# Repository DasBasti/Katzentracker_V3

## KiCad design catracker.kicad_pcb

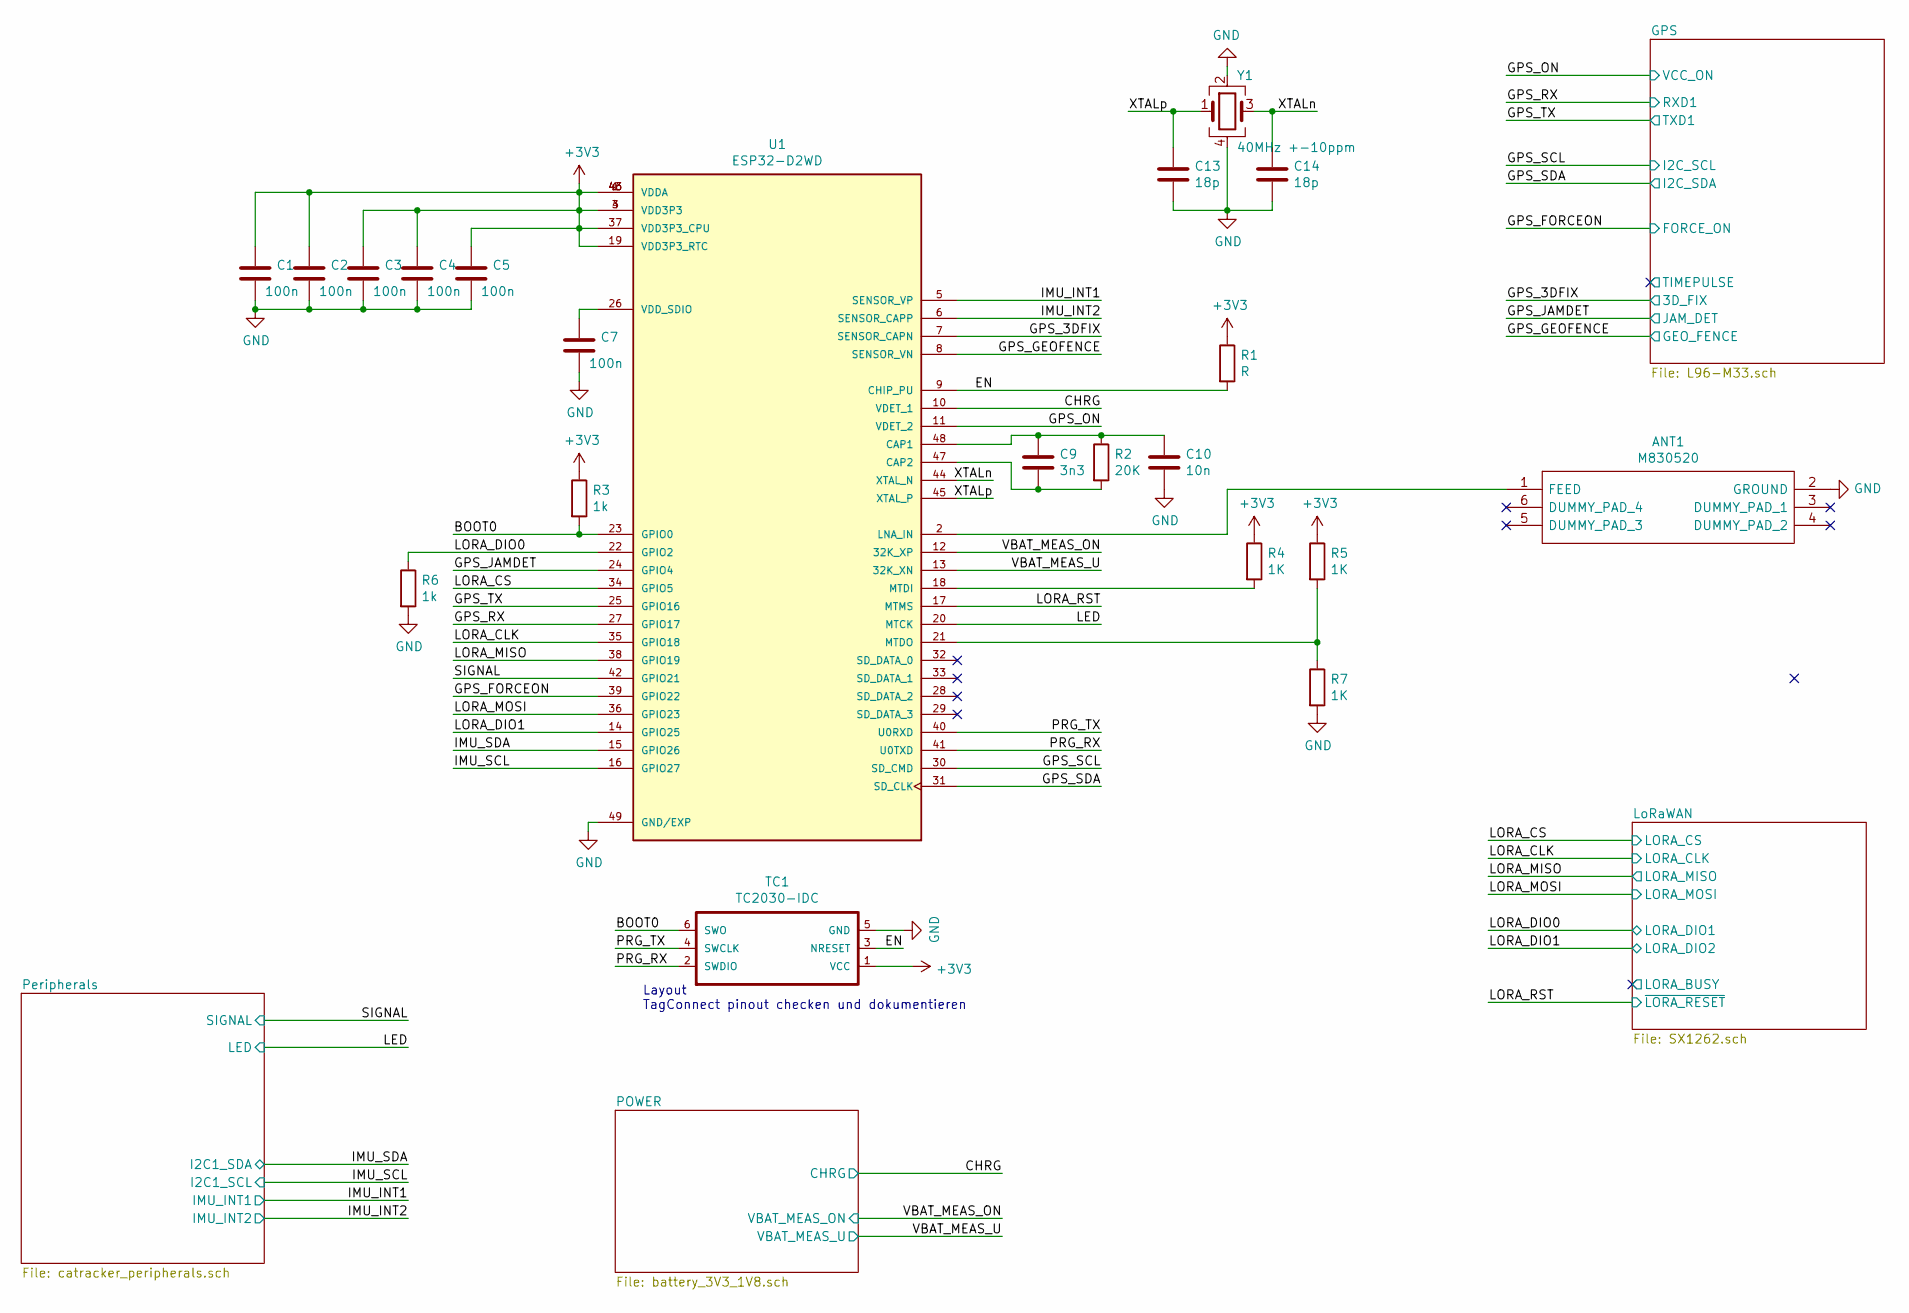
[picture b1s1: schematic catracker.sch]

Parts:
ANT1: M830520; Manufacturer_Part_Number M830520; Mouser Part Number 581-M830520
C1, C2, C3, C4, C5, C7: 100n; C_0402_1005Metric
C9: 3n3; C_0402_1005Metric
C10: 10n; C_0402_1005Metric
C13, C14: 18p; C_0402_1005Metric
R1: R; R_0402_1005Metric
R2: 20K; R_0402_1005Metric
R3, R6: 1k; R_0402_1005Metric
R4, R5, R7: 1K; R_0402_1005Metric
TC1: TC2030-IDC; Tag-Connect_TC2030-IDC-NL_2x03_P1.27mm_Vertical
U1: ESP32-D2WD; QFN-48-1EP_5x5mm_P0.35mm_EP3.7x3.7mm; PARTREV 2.9
Y1: 40MHz +-10ppm; Crystal_SMD_2520-4Pin_2.5x2.0mm

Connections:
+3V3: C1.1, C2.1, C3.1, C4.1, C5.1, R1.1, R3.1, R4.1, R5.1, TC1.1 (VCC), U1.1 (VDDA), U1.3 (VDD3P3), U1.4 (VDD3P3), U1.19 (VDD3P3_RTC), U1.37 (VDD3P3_CPU), U1.43 (VDDA), U1.46 (VDDA); also elsewhere on the board
/BOOT0: R3.2, TC1.6 (SWO), U1.23 (GPIO0)
/CHRG: U1.10 (VDET_1); also elsewhere on the board
/EN: R1.2, TC1.3 (NRESET), U1.9 (CHIP_PU)
/GPS_3DFIX: U1.7 (SENSOR_CAPN); also elsewhere on the board
/GPS_FORCEON: U1.39 (GPIO22); also elsewhere on the board
/GPS_GEOFENCE: U1.8 (SENSOR_VN); also elsewhere on the board
/GPS_JAMDET: U1.24 (GPIO4); also elsewhere on the board
/GPS_ON: U1.11 (VDET_2); also elsewhere on the board
/GPS_RX: U1.27 (GPIO17); also elsewhere on the board
/GPS_SCL: U1.30 (SD_CMD); also elsewhere on the board
/GPS_SDA: U1.31 (SD_CLK); also elsewhere on the board
/GPS_TX: U1.25 (GPIO16); also elsewhere on the board
/IMU_INT1: U1.5 (SENSOR_VP); also elsewhere on the board
/IMU_INT2: U1.6 (SENSOR_CAPP); also elsewhere on the board
/IMU_SCL: U1.16 (GPIO27); also elsewhere on the board
/IMU_SDA: U1.15 (GPIO26); also elsewhere on the board
/LED: U1.20 (MTCK); also elsewhere on the board
/LORA_CLK: U1.35 (GPIO18); also elsewhere on the board
/LORA_CS: U1.34 (GPIO5); also elsewhere on the board
/LORA_DIO0: R6.1, U1.22 (GPIO2); also elsewhere on the board
/LORA_DIO1: U1.14 (GPIO25); also elsewhere on the board
/LORA_MISO: U1.38 (GPIO19); also elsewhere on the board
/LORA_MOSI: U1.36 (GPIO23); also elsewhere on the board
/LORA_RST: U1.17 (MTMS); also elsewhere on the board
/PRG_RX: TC1.2 (SWDIO), U1.41 (U0TXD)
/PRG_TX: TC1.4 (SWCLK), U1.40 (U0RXD)
/SIGNAL: U1.42 (GPIO21); also elsewhere on the board
/VBAT_MEAS_ON: U1.12 (32K_XP); also elsewhere on the board
/VBAT_MEAS_U: U1.13 (32K_XN); also elsewhere on the board
/XTALn: C14.1, U1.44 (XTAL_N), Y1.3
/XTALp: C13.1, U1.45 (XTAL_P), Y1.1
GND: ANT1.2 (GROUND), C1.2, C2.2, C3.2, C4.2, C5.2, C7.2, C10.2, C13.2, C14.2, R6.2, R7.2, TC1.5 (GND), U1.49 (GND/EXP), Y1.2, Y1.4; also elsewhere on the board
unnamed: ANT1.1 (FEED), U1.2 (LNA_IN)
unnamed: C7.1, U1.26 (VDD_SDIO)
unnamed: C9.2, R2.2, U1.47 (CAP2)
unnamed: C9.1, C10.1, R2.1, U1.48 (CAP1)
unnamed: R4.2, U1.18 (MTDI)
unnamed: R5.2, R7.1, U1.21 (MTDO)

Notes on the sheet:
Layout TagConnect pinout checken und dokumentieren

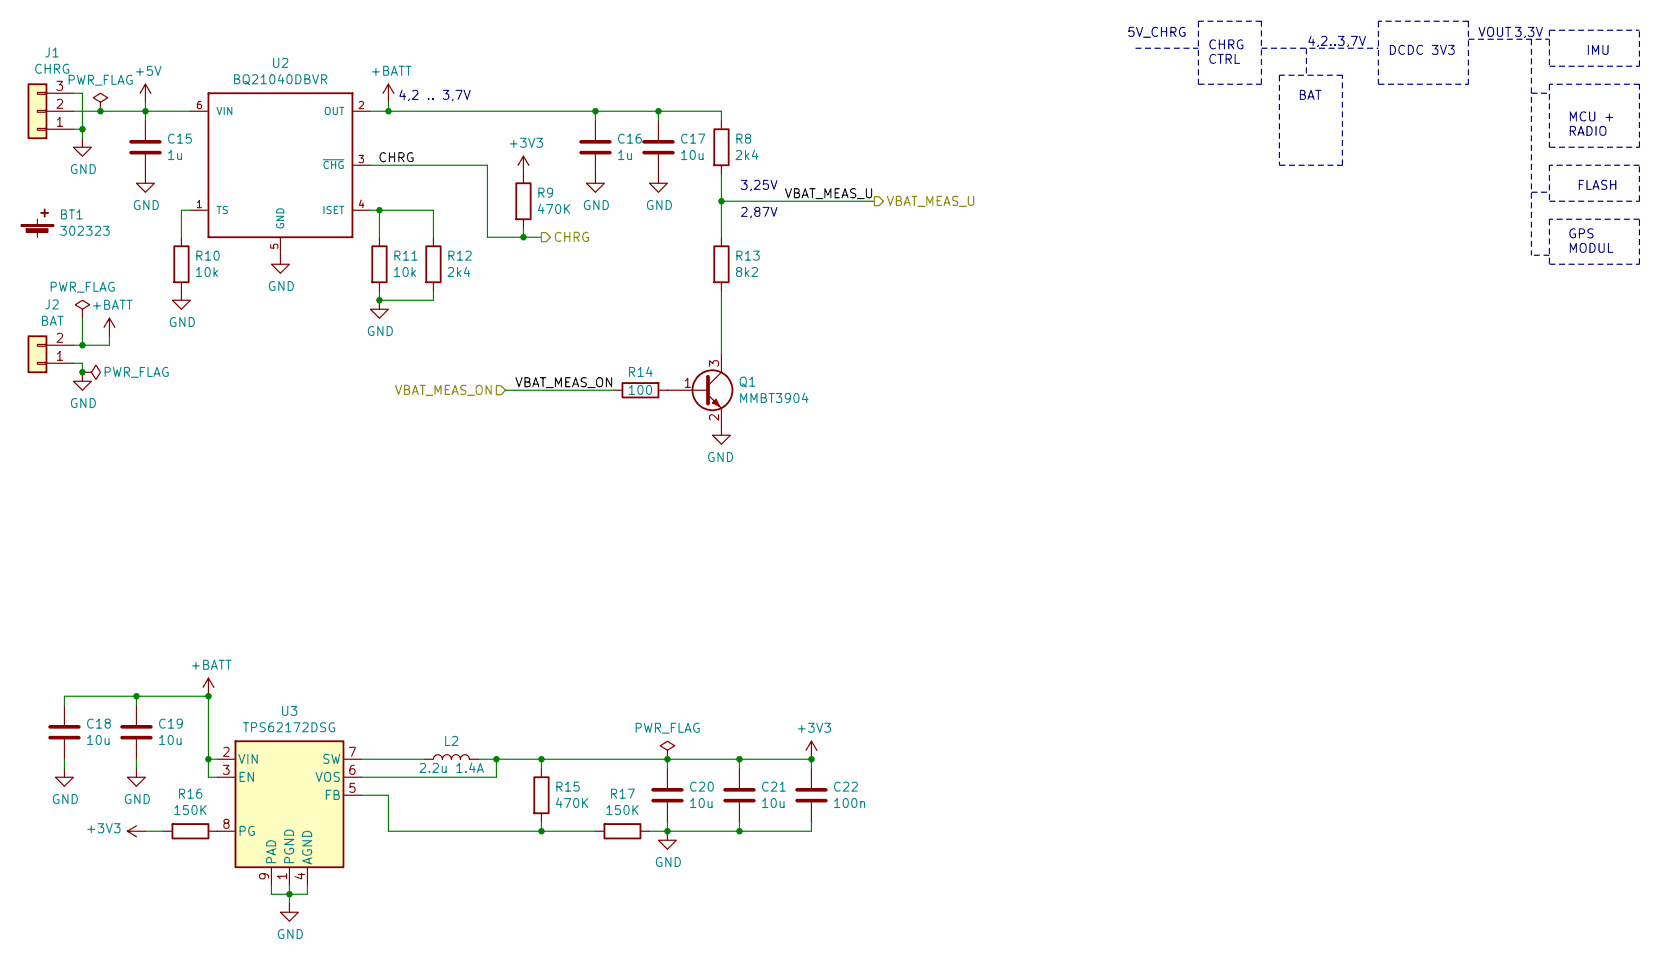
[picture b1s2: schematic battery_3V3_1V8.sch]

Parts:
BT1: 302323; LiPo_302323
C15, C16: 1u; C_0603_1608Metric; MPN 0603DC105MAT2A
C17, C18, C19, C20: 10u; C_0603_1608Metric; MPN GRM188R60J106ME84J
C21: 10u; C_0603_1608Metric; MPN 0603DC105MAT2A
C22: 100n; C_0402_1005Metric; MPN C1608X7R1V105K080AC
J1: CHRG; Magnetic_Charger_Clip
J2: BAT; PinSocket_1x02_P2.00mm_Vertical
L2: 2.2u 1.4A; L_0805_2012Metric; MPN AISC-0805F-2R2G-T
Q1: MMBT3904; SOT-23; MPN MMBT3904,215
R8, R12: 2k4; R_0402_1005Metric; MPN CRCW060310K0JNEAC
R9, R15: 470K; R_0402_1005Metric; MPN RC0603JR-138K2L
R10, R11: 10k; R_0402_1005Metric; MPN CRCW060310K0JNEAC
R13: 8k2; R_0402_1005Metric; MPN RC0603JR-138K2L
R14: 100; R_0402_1005Metric; MPN AC0603FR-13100RL
R16, R17: 150K; R_0402_1005Metric
U2: BQ21040DBVR; SOT-23-6; MPN BQ21040DBVR
U3: TPS62172DSG; WSON-8-1EP_2x2mm_P0.5mm_EP0.9x1.6mm_ThermalVias

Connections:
+3V3: C20.1, C21.1, C22.1, L2.2, R9.1, R15.1, R16.2, U3.6 (VOS); also elsewhere on the board
+5V: C15.1, J1.2, U2.6 (VIN)
+BATT: C16.1, C17.1, C18.1, C19.1, J2.2, R8.1, U2.2 (OUT), U3.2 (VIN), U3.3 (EN); also elsewhere on the board
/CHRG: R9.2, U2.3 (~CHG~); also elsewhere on the board
/VBAT_MEAS_ON: R14.1; also elsewhere on the board
/VBAT_MEAS_U: R8.2, R13.1; also elsewhere on the board
GND: C15.2, C16.2, C17.2, C18.2, C19.2, C20.2, C21.2, C22.2, J1.1, J1.3, J2.1, Q1.2 (E), R10.2, R11.2, R12.2, R17.1, U2.5 (GND), U3.1 (PGND), U3.4 (AGND), U3.9 (PAD); also elsewhere on the board
unnamed: L2.1, U3.7 (SW)
unnamed: Q1.1 (B), R14.2
unnamed: Q1.3 (C), R13.2
unnamed: R10.1, U2.1 (TS)
unnamed: R11.1, R12.1, U2.4 (ISET)
unnamed: R15.2, R17.2, U3.5 (FB)
unnamed: R16.1, U3.8 (PG)

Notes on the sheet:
3,25V
2,87V
4,2 .. 3,7V
FLASH
3,3V
4,2..3,7V
VOUT
IMU
MCU + RADIO
DCDC 3V3
5V_CHRG
CHRG CTRL
BAT
GPS MODUL

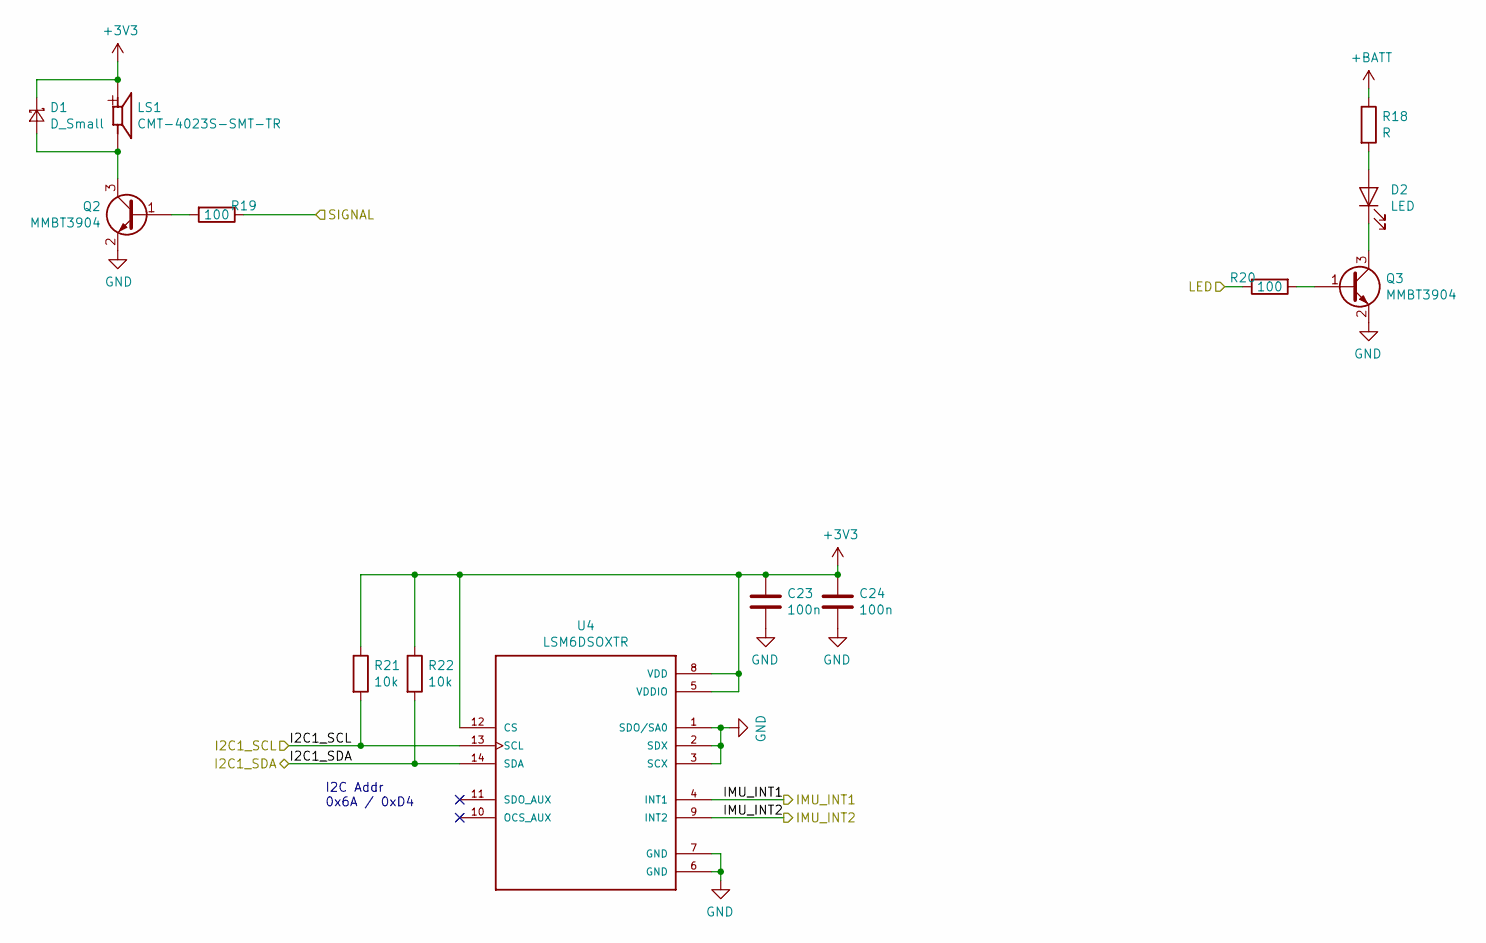
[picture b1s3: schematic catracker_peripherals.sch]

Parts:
C23, C24: 100n; C_0402_1005Metric; MPN C1608X7R1V105K080AC
D1: D_Small; D_0603_1608Metric_Pad1.05x0.95mm_HandSolder; MPN CDBURT0530LL-HF
D2: LED; LED_D3.0mm_smd
LS1: CMT-4023S-SMT-TR; CUI_CMT-4023S-SMT-TR; MPN CMT-4023S-SMT-TR
Q2, Q3: MMBT3904; SOT-23; MPN MMBT3904,215
R18: R; R_0402_1005Metric
R19, R20: 100; R_0402_1005Metric; MPN AC0603FR-13100RL
R21, R22: 10k; R_0402_1005Metric; MPN CRCW060310K0JNEAC
U4: LSM6DSOXTR; PQFN50P250X300X86-14N; MPN LSM6DSOXTR

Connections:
+3V3: C23.1, C24.1, D1.1 (K), LS1.P, R21.1, R22.1, U4.5 (VDDIO), U4.8 (VDD), U4.12 (CS); also elsewhere on the board
+BATT: R18.1; also elsewhere on the board
/IMU_INT1: U4.4 (INT1); also elsewhere on the board
/IMU_INT2: U4.9 (INT2); also elsewhere on the board
/IMU_SCL: R21.2, U4.13 (SCL); also elsewhere on the board
/IMU_SDA: R22.2, U4.14 (SDA); also elsewhere on the board
/LED: R20.1; also elsewhere on the board
/SIGNAL: R19.1; also elsewhere on the board
GND: C23.2, C24.2, Q2.2 (E), Q3.2 (E), U4.1 (SDO/SA0), U4.2 (SDX), U4.3 (SCX), U4.6 (GND), U4.7 (GND); also elsewhere on the board
unnamed: D1.2 (A), LS1.N, Q2.3 (C)
unnamed: D2.1 (K), Q3.3 (C)
unnamed: D2.2 (A), R18.2
unnamed: Q2.1 (B), R19.2
unnamed: Q3.1 (B), R20.2

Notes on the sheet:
I2C Addr 0x6A / 0xD4

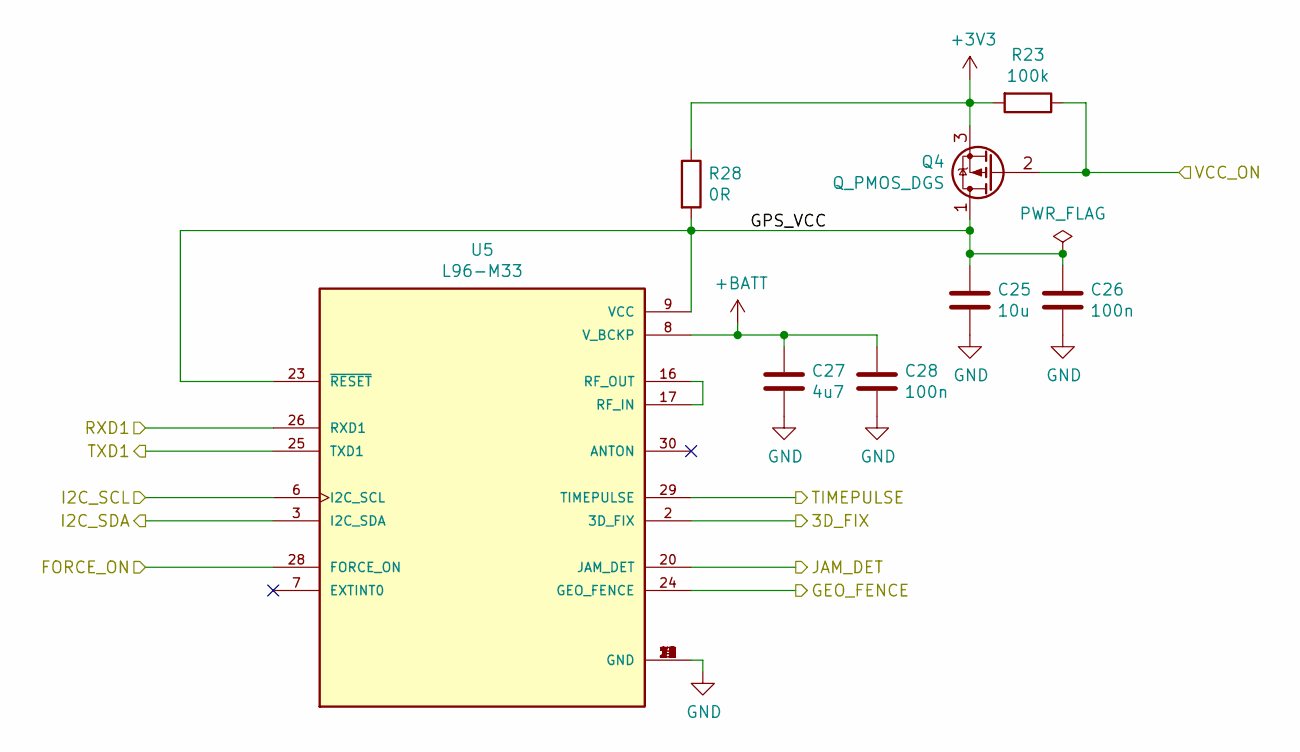
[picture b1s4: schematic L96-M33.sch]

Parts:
C25: 10u; C_0603_1608Metric
C26, C28: 100n; C_0402_1005Metric
C27: 4u7; C_0603_1608Metric
Q4: Q_PMOS_DGS; SOT-723
R23: 100k; R_0402_1005Metric
R28: 0R; R_0402_1005Metric
U5: L96-M33; XCVR_L96-M33

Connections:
+3V3: Q4.3 (S), R23.2, R28.1; also elsewhere on the board
+BATT: C27.1, C28.1, U5.8 (V_BCKP); also elsewhere on the board
/GPS/GPS_VCC: C25.1, C26.1, Q4.1 (D), R28.2, U5.9 (VCC), U5.23 (~RESET)
/GPS/TIMEPULSE: U5.29 (TIMEPULSE)
/GPS_3DFIX: U5.2 (3D_FIX); also elsewhere on the board
/GPS_FORCEON: U5.28 (FORCE_ON); also elsewhere on the board
/GPS_GEOFENCE: U5.24 (GEO_FENCE); also elsewhere on the board
/GPS_JAMDET: U5.20 (JAM_DET); also elsewhere on the board
/GPS_ON: Q4.2 (G), R23.1; also elsewhere on the board
/GPS_RX: U5.26 (RXD1); also elsewhere on the board
/GPS_SCL: U5.6 (I2C_SCL); also elsewhere on the board
/GPS_SDA: U5.3 (I2C_SDA); also elsewhere on the board
/GPS_TX: U5.25 (TXD1); also elsewhere on the board
GND: C25.2, C26.2, C27.2, C28.2, U5.4 (GND), U5.5 (GND), U5.10 (GND), U5.11 (GND), U5.12 (GND), U5.13 (GND), U5.14 (GND), U5.15 (GND), U5.18 (GND), U5.19 (GND), U5.21 (GND), U5.22 (GND), U5.27 (GND), U5.31 (GND); also elsewhere on the board
unnamed: U5.16 (RF_OUT), U5.17 (RF_IN)

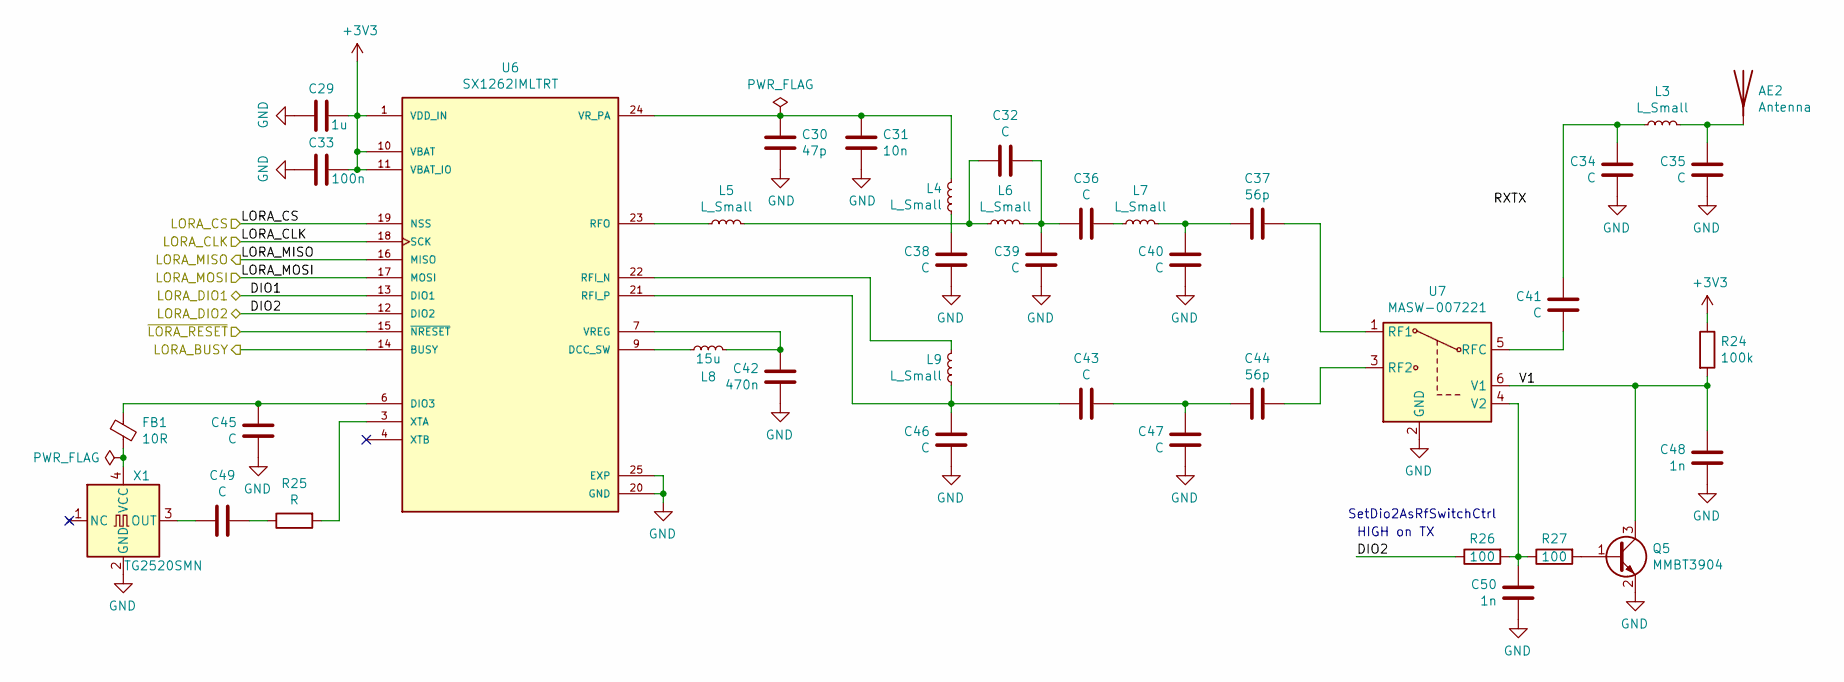
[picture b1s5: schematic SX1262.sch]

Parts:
AE2: Antenna; TestPoint_THTPad_D2.0mm_Drill1.0mm
C29: 1u; C_0603_1608Metric
C30: 47p; C_0402_1005Metric
C31: 10n; C_0402_1005Metric
C32, C34, C35, C36, C38, C39, C40, C41, C43, C45, C46, C47, C49: C; C_0402_1005Metric
C33: 100n; C_0402_1005Metric
C37, C44: 56p; C_0402_1005Metric
C42: 470n; C_0402_1005Metric
C48, C50: 1n; C_0402_1005Metric
FB1: 10R; L_0603_1608Metric
L3, L4, L5, L6, L7, L9: L_Small; L_0402_1005Metric
L8: 15u; L_0402_1005Metric
Q5: MMBT3904; SOT-23; MPN MMBT3904,215
R24: 100k; R_0402_1005Metric
R25: R; R_0402_1005Metric
R26, R27: 100; R_0402_1005Metric; MPN AC0603FR-13100RL
U6: SX1262IMLTRT; QFN50P400X400X100-25N; PARTREV 1.1
U7: MASW-007221; SOT-363_SC-70-6
X1: TG2520SMN; Oscillator_SMD_TXC_7C-4Pin_5.0x3.2mm

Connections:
+3V3: C29.2, C33.2, R24.1, U6.1 (VDD_IN), U6.10 (VBAT), U6.11 (VBAT_IO); also elsewhere on the board
/LORA_CLK: U6.18 (SCK); also elsewhere on the board
/LORA_CS: U6.19 (NSS); also elsewhere on the board
/LORA_DIO0: U6.13 (DIO1); also elsewhere on the board
/LORA_DIO1: R26.1, U6.12 (DIO2); also elsewhere on the board
/LORA_MISO: U6.16 (MISO); also elsewhere on the board
/LORA_MOSI: U6.17 (MOSI); also elsewhere on the board
/LORA_RST: U6.15 (~NRESET); also elsewhere on the board
/LoRaWAN/LORA_BUSY: U6.14 (BUSY)
/LoRaWAN/V1: C48.2, Q5.3 (C), R24.2, U7.6 (V1)
GND: C29.1, C30.1, C31.1, C33.1, C34.1, C35.1, C38.2, C39.1, C40.1, C42.2, C45.2, C46.2, C47.2, C48.1, C50.1, Q5.2 (E), U6.2 (GND), U6.5 (GND), U6.8 (GND), U6.20 (GND), U6.25 (EXP), U7.2 (GND), X1.2 (GND); also elsewhere on the board
unnamed: AE2.1, C35.2, L3.1
unnamed: C30.2, C31.2, L4.1, U6.24 (VR_PA)
unnamed: C32.1, C38.1, L4.2, L5.1, L6.2
unnamed: C32.2, C36.1, C39.2, L6.1
unnamed: C34.2, C41.2, L3.2
unnamed: C36.2, L7.2
unnamed: C37.1, C40.2, L7.1
unnamed: C37.2, U7.1 (RF1)
unnamed: C41.1, U7.5 (RFC)
unnamed: C42.1, L8.1, U6.7 (VREG)
unnamed: C43.1, C46.1, L9.2, U6.21 (RFI_P)
unnamed: C43.2, C44.1, C47.1
unnamed: C44.2, U7.3 (RF2)
unnamed: C45.1, FB1.1, U6.6 (DIO3)
unnamed: C49.1, X1.3 (OUT)
unnamed: C49.2, R25.1
unnamed: C50.2, R26.2, R27.1, U7.4 (V2)
unnamed: FB1.2, X1.4 (VCC)
unnamed: L5.2, U6.23 (RFO)
unnamed: L8.2, U6.9 (DCC_SW)
unnamed: L9.1, U6.22 (RFI_N)
unnamed: Q5.1 (B), R27.2
unnamed: R25.2, U6.3 (XTA)

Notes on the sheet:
HIGH on TX
SetDio2AsRfSwitchCtrl

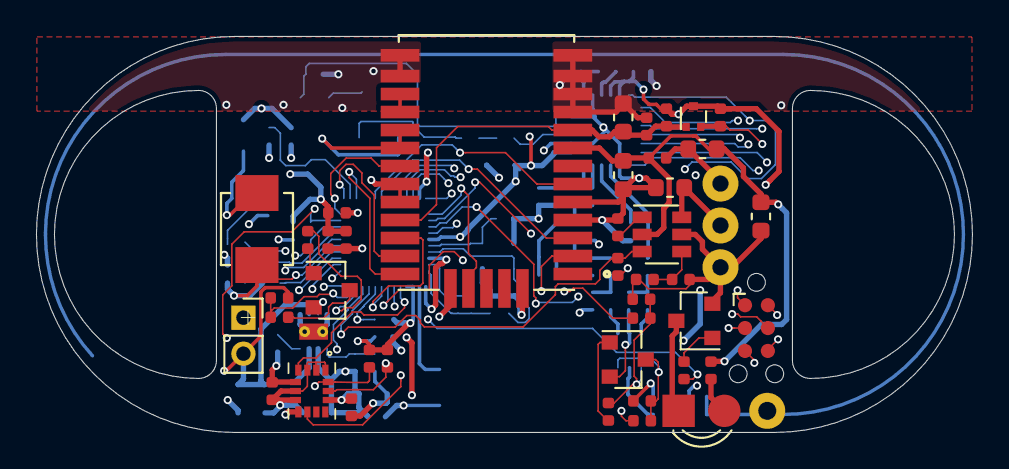
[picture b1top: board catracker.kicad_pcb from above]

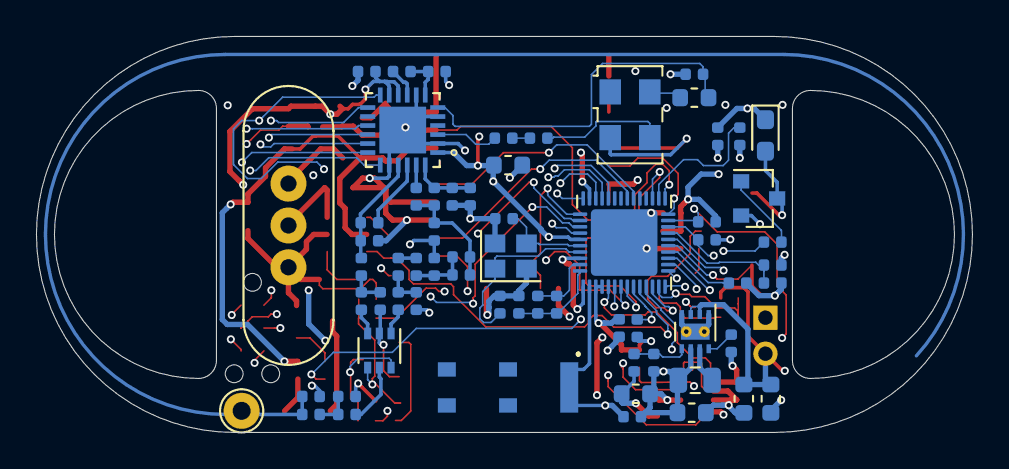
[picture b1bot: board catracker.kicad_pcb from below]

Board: 4 copper layers, 52.0 x 22.0 mm, 106 parts (65 on the bottom side), 79 nets.

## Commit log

2021-06-07 layout complete
